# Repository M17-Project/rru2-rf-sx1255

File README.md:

# RRU2 RF SX1255

This is an M.2 RF card for the M17 Remote Radio Unit v2 (RRU v2). The card
has the Semtech SX1255 transceiver for the 400 MHz to 510 MHz band. You can
replace the card with a card for a different band or a different chip. The
mainboard with the Raspberry Pi CM4 or CM5 stays the same. You can also use
the card without the RRU.

Revision A.

## Status

Work in progress. Not tested. Do not order.

## Block diagram

This diagram is preliminary. It can change.

```mermaid
flowchart LR
    M2["M.2 key E edge connector<br/>3.3 V, SPI with chip selects, I2S,<br/>I2C for control, ID_SD/ID_SC,<br/>GPIO, 10 MHz reference, PPS"]

    EEPROM["ID EEPROM<br/>Raspberry Pi HAT format"]
    PLL["ADF4002 PLL"]
    TCXO["32 MHz VCTCXO"]
    SX["SX1255 transceiver"]
    AMP["HMC374 amplifier"]
    ATT["3x PE4312<br/>digital step attenuator"]
    TXC["U.FL TX"]
    RXC["U.FL RX"]

    M2 -- "ID_SD, ID_SC" --> EEPROM
    M2 -- "SPI" --> SX
    M2 -- "SPI" --> ATT
    M2 <-->|"I2S"| SX

    M2 -- "10 MHz" --> PLL
    PLL -- "tune" --> TCXO
    TCXO -- "32 MHz" --> PLL
    TCXO -- "32 MHz" --> SX

    SX -- "TX" --> AMP
    AMP --> TXC

    RXC --> ATT
    ATT -- "RX" --> SX
```

The card has no other RF connectors. The M.2 connector has only power and
digital signals. The RF signals go through the two U.FL connectors.

## Key facts

| Item | Value |
|---|---|
| Form factor | M.2 key E, size 2230 or 2242 (not decided) |
| Board | 0.8 mm, 4 layers, JLCPCB stackup JLC04081H-7628 |
| RF connectors | 2x U.FL (TX and RX) |
| Frequency range | 400 MHz to 510 MHz (SX1255) |
| Output power | 22 dBm (P1dB) |

## Repository

This is a KiCad 10 project. The KiCad library is the git submodule `lib`. It is
the [M17 KiCad library](https://github.com/M17-Project/M17_kicad_library).
The [library README](https://github.com/M17-Project/M17_kicad_library#readme)
tells how to add parts.

### Get the files

Clone the repository with the library submodule:

```sh
git clone --recursive https://github.com/M17-Project/rru2-rf-sx1255.git
```

If you cloned without `--recursive`, get the library:

```sh
git submodule update --init
```

### Build

Install KiCad 10 and KiKit. Then run:

```sh
make
```

The build checks the design first. Any ERC or DRC violation stops the build.
Each part on the BOM must have a Mouser number or a source. The outputs are in `build/`.

To use the same tools as the CI, run the build in Docker:

```sh
make docker
```

To run only the checks, run:

```sh
make check
```

This target runs the ERC, the DRC with the schematic parity check, and the BOM
check. Any violation is an error.

### Update the library

```sh
make lib-update
```

Then open the project in KiCad and update the symbols and footprints.
Commit the `lib` submodule change together with the design change.

## License

This work is licensed under a
[Creative Commons Attribution-NonCommercial-ShareAlike 4.0 International License][cc-by-nc-sa].
Refer to `LICENSE.txt`.

[![CC BY-NC-SA 4.0][cc-by-nc-sa-image]][cc-by-nc-sa]

[cc-by-nc-sa]: http://creativecommons.org/licenses/by-nc-sa/4.0/
[cc-by-nc-sa-image]: https://licensebuttons.net/l/by-nc-sa/4.0/88x31.png

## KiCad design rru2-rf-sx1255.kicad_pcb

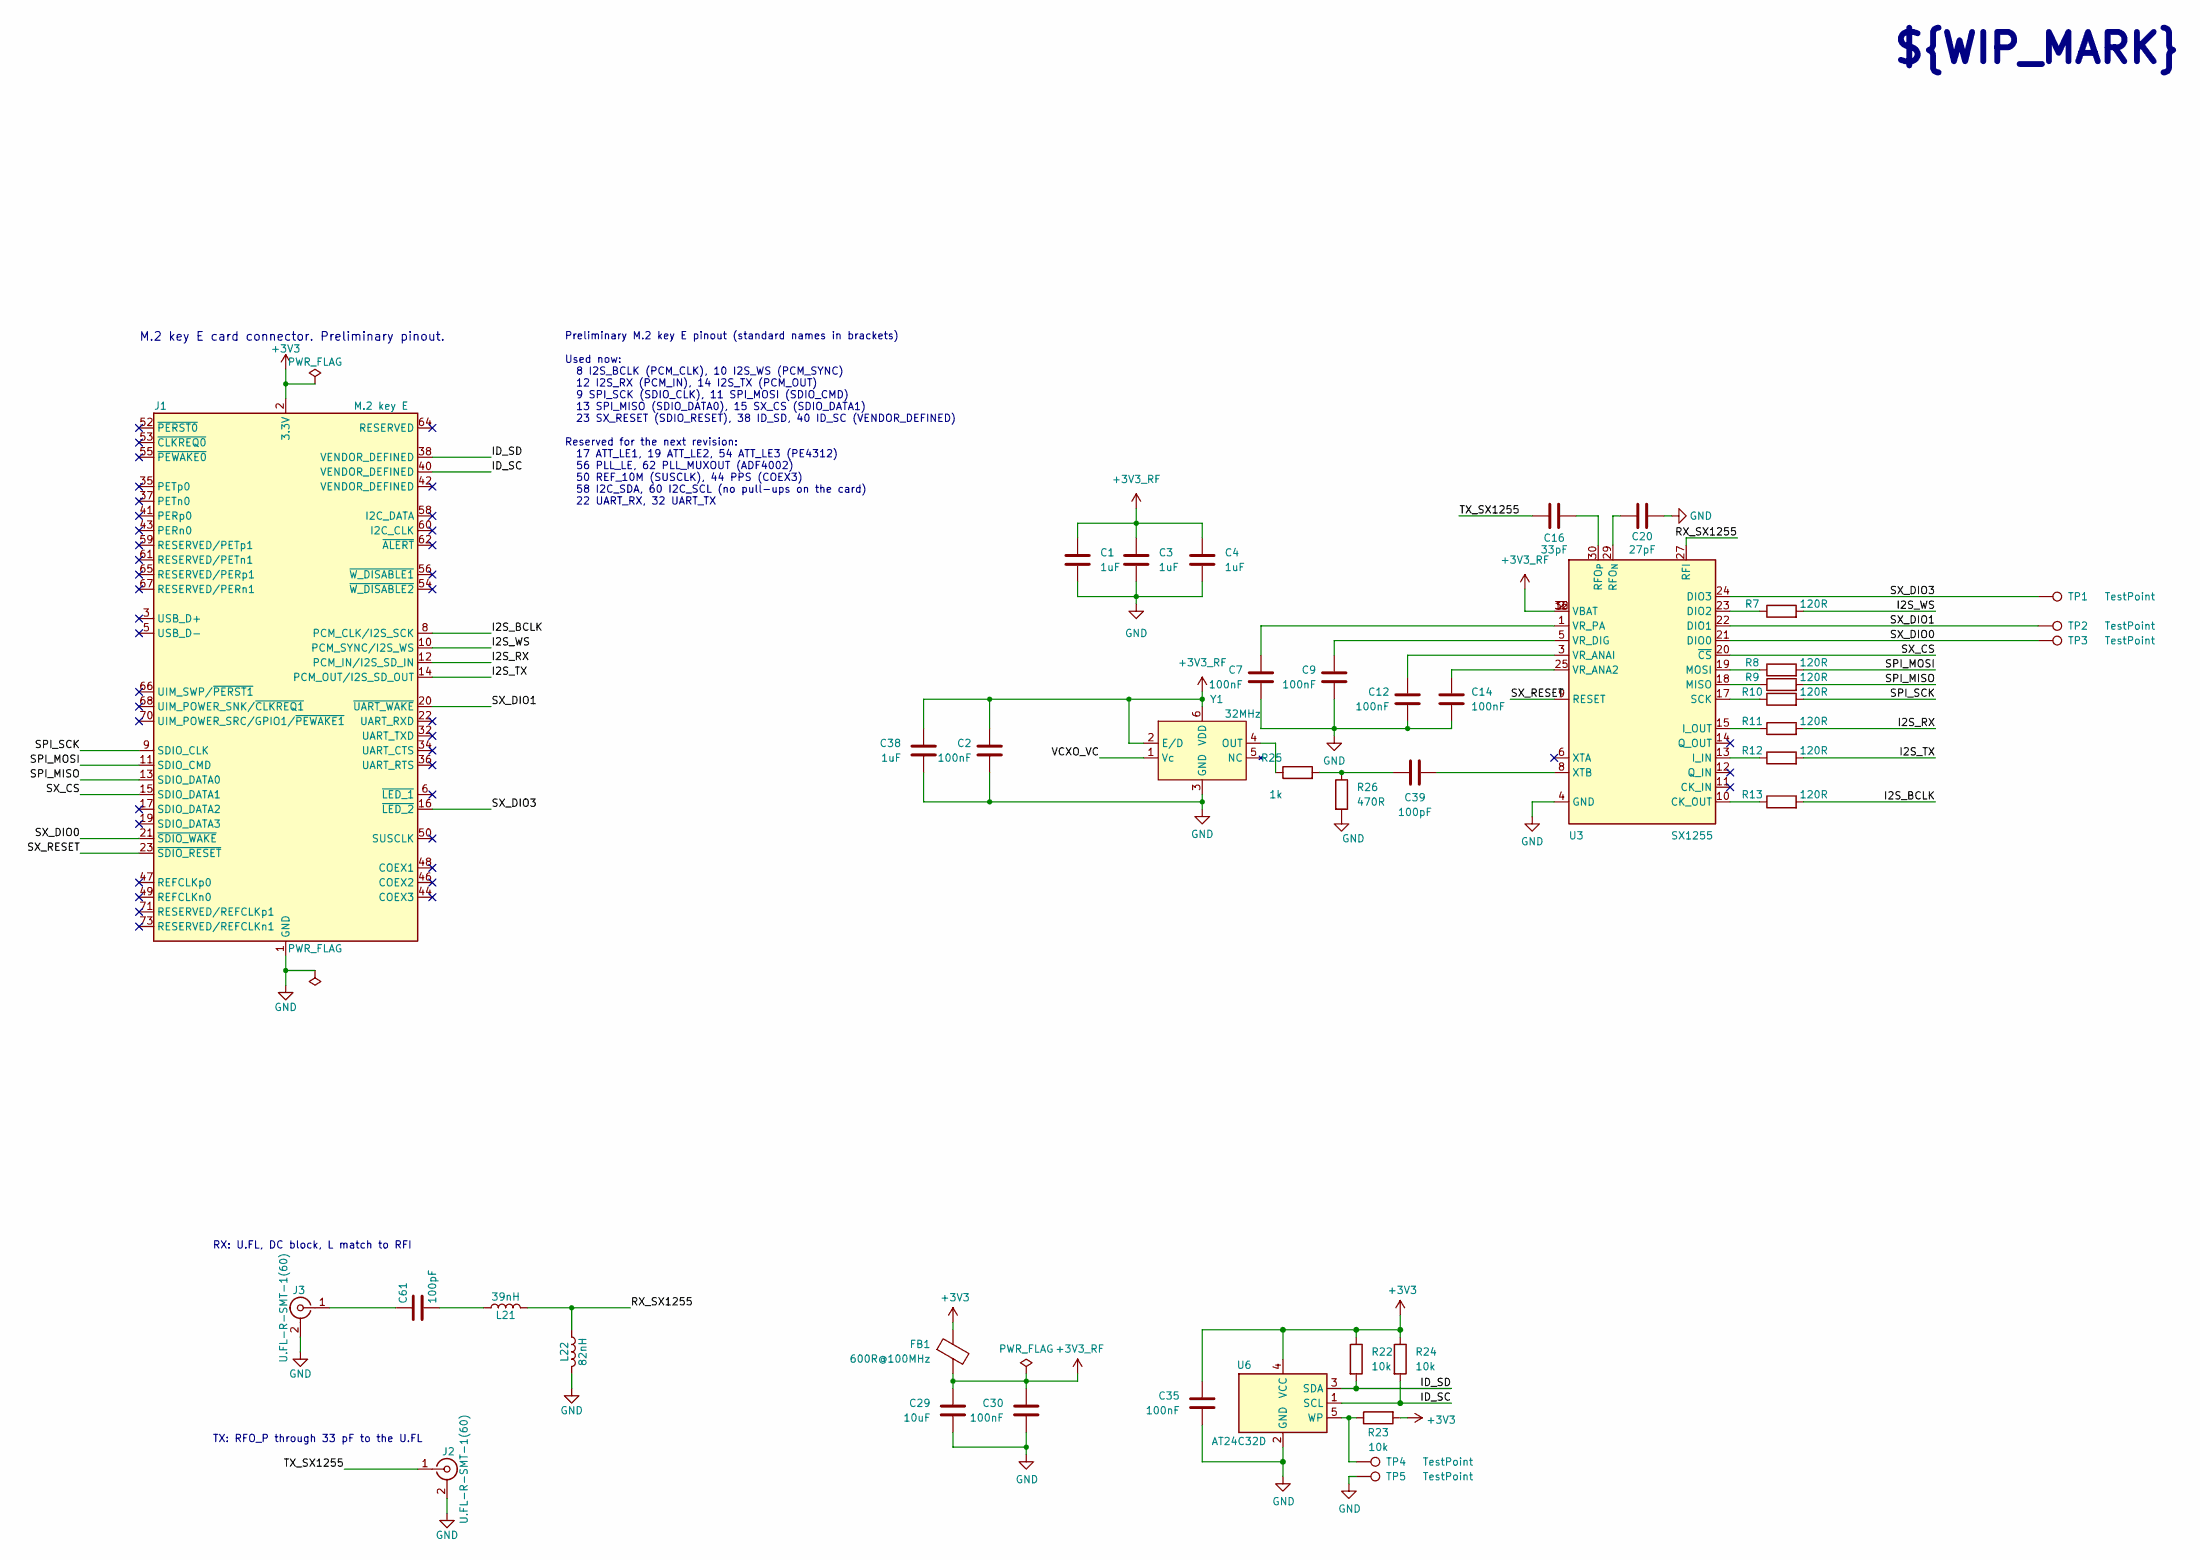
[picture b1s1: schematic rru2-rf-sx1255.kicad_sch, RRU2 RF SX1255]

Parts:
C1, C3, C4, C38: 1uF; C_0402_1005Metric; Tolerance ±10%; Voltage 25V; MPN CL05A105KA5NQNC; Mouser 187-CL05A105KA5NQNC
C2, C7, C9, C12, C14, C30, C35: 100nF; C_0402_1005Metric; Tolerance ±10%; Voltage 50V; MPN CL05B104KB54PNC; Mouser 187-CL05B104KB54PNC
C16: 33pF; C_0402_1005Metric; Tolerance ±1%; Voltage 50V; MPN GJM1555C1H330FB01D; Mouser 81-GJM1555C1H330FB1D
C20: 27pF; C_0402_1005Metric; Tolerance ±1%; Voltage 50V; MPN GJM1555C1H270FB01D; Mouser 81-GJM1555C1H270FB1D
C29: 10uF; C_0805_2012Metric; Tolerance ±10%; Voltage 50V; MPN CL21A106KBYQNNE; Mouser 187-CL21A106KBYQNNE
C39, C61: 100pF; C_0402_1005Metric; Tolerance ±2%; Voltage 100V; MPN GCM1555C2A101GE02D; Mouser 81-GCM1555C2A101GE2D
FB1: 600R@100MHz; L_0402_1005Metric; Tolerance ±25%; MPN BLM15PX601SN1D; Mouser 81-BLM15PX601SN1D
J1: M.2 key E; M.2_2242-xx-E
J2, J3: U.FL-R-SMT-1(60); U.FL_Hirose_U.FL-R-SMT-1_Vertical; MPN U.FL-R-SMT-1(60); Mouser 798-UFLRSMT160
L21: 39nH; L_0402_1005Metric; Tolerance ±2%; MPN LQW15AN39NG00D; Mouser 81-LQW15AN39NG00D
L22: 82nH; L_0402_1005Metric; Tolerance ±2%; MPN LQW15AN82NG00D; Mouser 81-LQW15AN82NG00D
R7, R8, R9, R10, R11, R12, R13: 120R; R_0402_1005Metric; Tolerance ±1%; Voltage 50V; MPN 0402WGF1200TCE; Mouser 303-0402WGF1200TCE
R22, R23, R24: 10k; R_0402_1005Metric; Tolerance ±1%; Voltage 50V; MPN 0402WGF1002TCE; Mouser 303-0402WGF1002TCE
R25: 1k; R_0402_1005Metric; Tolerance ±1%; Voltage 50V; MPN 0402WGF1001TCE; Mouser 303-0402WGF1001TCE
R26: 470R; R_0402_1005Metric; Tolerance ±1%; Voltage 50V; MPN 0402WGF4700TCE; Mouser 303-0402WGF4700TCE
TP1, TP2, TP3, TP4, TP5: TestPoint; TestPoint_Pad_D1.0mm
U3: SX1255; QFN-32-1EP_5x5mm_P0.5mm_EP3.3x3.3mm_ThermalVias; Mouser Part Number 947-SX1255IWLTRT
U6: AT24C32D; SOT-23-5; MPN AT24C32D-STUM-T; Mouser 556-AT24C32D-STUM-T
Y1: 32MHz; Oscillator_SMD_IDT_JS6-6_5.0x3.2mm_P1.27mm; MPN XLH53V032.000000I; Mouser 972-XLH53V032000000I

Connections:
+3V3: C35.1, FB1.1, J1.2 (3.3V), J1.4 (3.3V), J1.72 (3.3V), J1.74 (3.3V), R22.1, R23.2, R24.1, U6.4 (VCC)
+3V3_RF: C1.1, C2.1, C3.1, C4.1, C29.1, C30.1, C38.1, FB1.2, U3.2 (VBAT), U3.16 (VBAT), U3.32 (VBAT), Y1.2 (E/D), Y1.6 (VDD)
/I2S_BCLK: J1.8 (PCM_CLK/I2S_SCK), R13.2
/I2S_RX: J1.12 (PCM_IN/I2S_SD_IN), R11.2
/I2S_TX: J1.14 (PCM_OUT/I2S_SD_OUT), R12.2
/I2S_WS: J1.10 (PCM_SYNC/I2S_WS), R7.2
/ID_SC: J1.40 (VENDOR_DEFINED), R24.2, U6.1 (SCL)
/ID_SD: J1.38 (VENDOR_DEFINED), R22.2, U6.3 (SDA)
/RX_SX1255: L21.2, L22.1, U3.27 (RFI)
/SPI_MISO: J1.13 (SDIO_DATA0), R9.2
/SPI_MOSI: J1.11 (SDIO_CMD), R8.2
/SPI_SCK: J1.9 (SDIO_CLK), R10.2
/SX_CS: J1.15 (SDIO_DATA1), U3.20 (~CS)
/SX_DIO0: J1.21 (~SDIO_WAKE), TP3.1 (1_1), U3.21 (DIO0)
/SX_DIO1: J1.20 (~UART_WAKE), TP2.1 (1_1), U3.22 (DIO1)
/SX_DIO3: J1.16 (~LED_2), TP1.1 (1_1), U3.24 (DIO3)
/SX_RESET: J1.23 (~SDIO_RESET), U3.9 (RESET)
/TX_SX1255: C16.1, J2.1 (In)
/VCXO_VC: Y1.1 (Vc)
GND: C1.2, C2.2, C3.2, C4.2, C7.2, C9.2, C12.2, C14.2, C20.2, C29.2, C30.2, C35.2, C38.2, J1.1 (GND), J1.7 (GND), J1.18 (GND), J1.33 (GND), J1.39 (GND), J1.45 (GND), J1.51 (GND), J1.57 (GND), J1.63 (GND), J1.69 (GND), J1.75 (GND), J2.2 (Ext), J3.2 (Ext), L22.2, R26.2, TP5.1 (1_1), U3.4 (GND), U3.7 (GND), U3.26 (GND), U3.28 (GND), U3.31 (GND), U3.33 (GND), U6.2 (GND), Y1.3 (GND)
unnamed: C39.2, R25.2, R26.1
unnamed: C61.2, L21.1
unnamed: C61.1, J3.1 (In)
unnamed: R13.1, U3.10 (CK_OUT)
unnamed: R7.1, U3.23 (DIO2)
unnamed: R12.1, U3.13 (I_IN)
unnamed: R11.1, U3.15 (I_OUT)
unnamed: R9.1, U3.18 (MISO)
unnamed: R8.1, U3.19 (MOSI)
unnamed: C20.1, U3.29 (RFO_{N})
unnamed: C16.2, U3.30 (RFO_{P})
unnamed: R10.1, U3.17 (SCK)
unnamed: C14.1, U3.25 (VR_ANA2)
unnamed: C12.1, U3.3 (VR_ANAI)
unnamed: C9.1, U3.5 (VR_DIG)
unnamed: C7.1, U3.1 (VR_PA)
unnamed: C39.1, U3.8 (XTB)
unnamed: R23.1, TP4.1 (1_1), U6.5 (WP)
unnamed: R25.1, Y1.4 (OUT)

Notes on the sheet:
Preliminary M.2 key E pinout (standard names in brackets) Used now: 8 I2S_BCLK (PCM_CLK), 10 I2S_WS (PCM_SYNC) 12 I2S_RX (PCM_IN), 14 I2S_TX (PCM_OUT) 9 SPI_SCK (SDIO_CLK), 11 SPI_MOSI (SDIO_CMD) 13 SPI_MISO (SDIO_DATA0), 15 SX_CS (SDIO_DATA1) 23 SX_RESET (SDIO_RESET), 38 ID_SD, 40 ID_SC (VENDOR_DE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
M.2 key E card connector. Preliminary pinout.
TX: RFO_P through 33 pF to the U.FL
${WIP_MARK}
RX: U.FL, DC block, L match to RFI

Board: 4 copper layers, 42 parts (5 on the bottom side), 38 nets, no tracks yet.
